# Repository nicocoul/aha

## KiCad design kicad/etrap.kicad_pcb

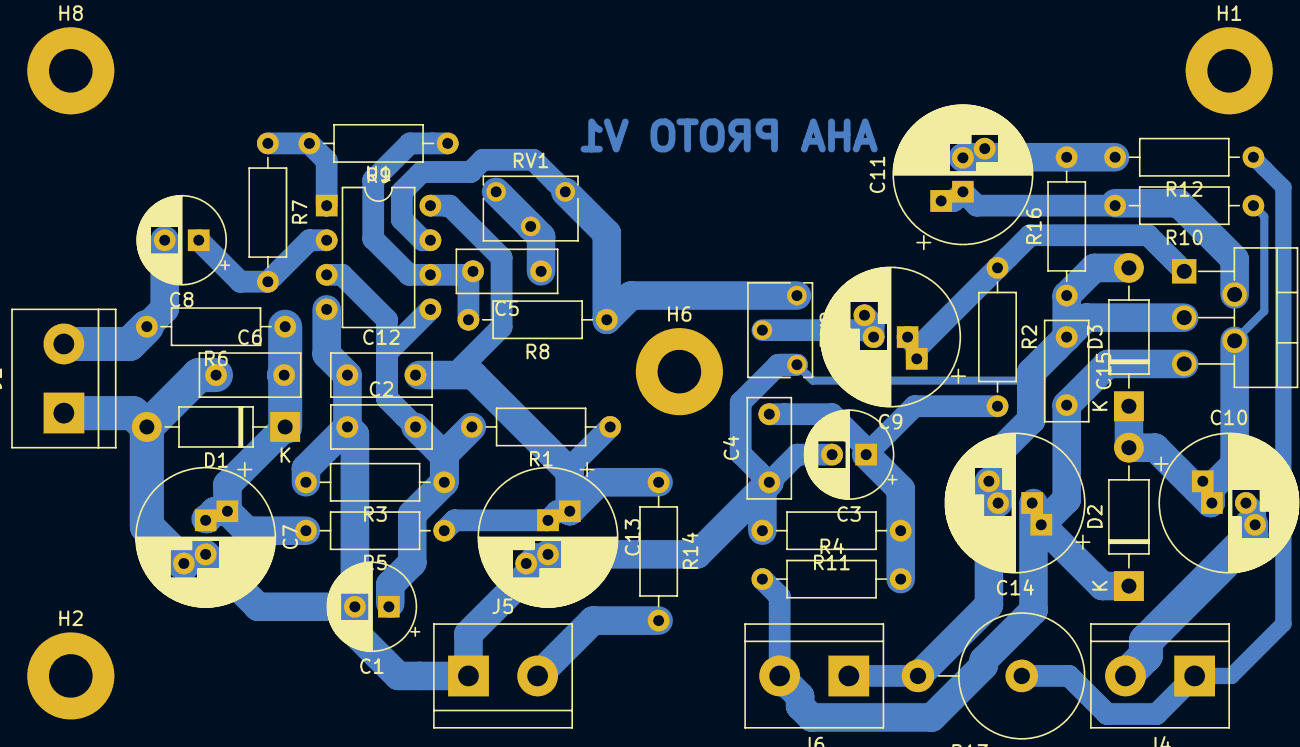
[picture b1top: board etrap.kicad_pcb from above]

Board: 2 copper layers, 45 parts (0 on the bottom side), 20 nets.

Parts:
C1, C3: 22u 16V; CP_Radial_D6.3mm_P2.50mm
C2, C4, C5, C6, C12, C15: 100n; C_Rect_L7.2mm_W3.0mm_P5.00mm_FKS2_FKP2_MKS2_MKP2
C7: 220u 16V; CP_Radial_D10.0mm_P2.50mm_P5.00mm
C8: 2.2u; CP_Radial_D6.3mm_P2.50mm
C9: 22u 16V; CP_Radial_D10.0mm_P2.50mm_P5.00mm
C10, C14: 2200u 35V; CP_Radial_D10.0mm_P2.50mm_P5.00mm
C11: 1000u 16V; CP_Radial_D10.0mm_P2.50mm_P5.00mm
C13: 220u 35V; CP_Radial_D10.0mm_P2.50mm_P5.00mm
D1: 9V; D_DO-41_SOD81_P10.16mm_Horizontal
D2, D3: 1N4001; D_DO-41_SOD81_P10.16mm_Horizontal
H1, H2, H6, H8: MountingHole; MountingHole_3.2mm_M3_Pad
J1: mic-in; TerminalBlock_bornier-2_P5.08mm
J4: amp-out; TerminalBlock_bornier-2_P5.08mm
J5, J6: power; TerminalBlock_bornier-2_P5.08mm
R1, R2, R3, R4, R8, R9, R10, R11: 22k; R_Axial_DIN0207_L6.3mm_D2.5mm_P10.16mm_Horizontal
R5: 220; R_Axial_DIN0207_L6.3mm_D2.5mm_P10.16mm_Horizontal
R6: 13.7k; R_Axial_DIN0207_L6.3mm_D2.5mm_P10.16mm_Horizontal
R7: 75k; R_Axial_DIN0207_L6.3mm_D2.5mm_P10.16mm_Horizontal
R12: 100; R_Axial_DIN0207_L6.3mm_D2.5mm_P10.16mm_Horizontal
R13: 0.47; R_Axial_DIN0918_L18.0mm_D9.0mm_P7.62mm_Vertical
R14: 1; R_Axial_DIN0207_L6.3mm_D2.5mm_P10.16mm_Horizontal
R16: 1k; R_Axial_DIN0207_L6.3mm_D2.5mm_P10.16mm_Horizontal
RV1: 1k; Potentiometer_Bourns_3266W_Vertical
RV2: 22k; Potentiometer_Bourns_3266W_Vertical
U1: NE5532; DIP-8_W7.62mm
U2: TDA2050; TO-220-5_P3.4x3.7mm_StaggerOdd_Lead3.8mm_Vertical

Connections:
GND: C1.2, C2.1, C3.2, C4.1, C6.1, C7.2, C12.1, C13.2, C14.2, C15.1, D1.2, D3.2, J1.1, J5.1, J6.1, R3.2, R11.2, R13.2, R16.1, RV2.1, U1.4, U2.3
unnamed: C3.1, C4.2, R2.2, R4.2, R11.1
unnamed: C5.1, RV1.2, RV1.3
unnamed: C5.2, R8.2, R9.1, U1.6
unnamed: C6.2, C7.1, D1.1, R5.2, R6.1
unnamed: C8.1, R7.2, U1.2
unnamed: C8.2, J1.2, R6.2
unnamed: C9.1, R2.1, U2.1
unnamed: C9.2, RV2.2
unnamed: C10.1, D2.2, D3.1, R10.1, U2.4
unnamed: C10.2, J4.2
unnamed: C11.1, R10.2, U2.2
unnamed: C11.2, R12.2, R16.2
unnamed: J4.1, R12.1, R13.1
unnamed: J5.2, R14.2
unnamed: R7.1, R9.2, U1.1
unnamed: R8.1, RV1.1, RV2.3, U1.7
VCC1: C12.2, C13.1, R1.1, R5.1, R14.1, U1.8
VCC2: C14.1, C15.2, D2.1, J6.2, R4.1, U2.5
VGND: C1.1, C2.2, R1.2, R3.1, U1.3, U1.5
